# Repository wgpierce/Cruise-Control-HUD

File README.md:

# Cruise-Control-HUD
Cruise control HUD MiniProject for ECE 362 and Purdue Spark Challenge

## Setup

Configuration and project files have been omitted since they carry no useful information
and are a pain to track

If you do want to use this code yourself, using CodeWarrior, do the following:

Open CodeWarrior, and navigate through these generic dialogs.
The setting we used are right below the corresponding generic tag.

File -> New Project -> \<family\> -> \<specific member\> -> \<whichever connections\> -> Next -> Finish                  
&nbsp;&nbsp;&nbsp;&nbsp;&nbsp;&nbsp;&nbsp;&nbsp;&nbsp;&nbsp;&nbsp;&nbsp;&nbsp;&nbsp;&nbsp;&nbsp;&nbsp;&nbsp;&nbsp;&nbsp;&nbsp;&nbsp;&nbsp;&nbsp;&nbsp;&nbsp; HCS12C FAMILY &nbsp;&nbsp;&nbsp;&nbsp; MC9S12C32 &nbsp;&nbsp;&nbsp;&nbsp;&nbsp;&nbsp;&nbsp;&nbsp;&nbsp;&nbsp;&nbsp;&nbsp;&nbsp;&nbsp;&nbsp;&nbsp;&nbsp;&nbsp; USB BDM Multilink 

After that, you can just copy the code from the main.c file in this repository to replace the main.c in 
your projectFolder/Sources/ folder
		
## Technologies used

#### Hardware
- MC9S12C32 microcontroller board
- OBD to UART Cable
- LIDAR
- Custom PCB with power wired to OBD board
- Shift Registers
- 4x7-segment Displays
- Printrbot Simple Metal

#### Software
- CodeWarrior
	- USBMLT
- Eagle
- Autodesk Fusion

See Documentation for more specific details

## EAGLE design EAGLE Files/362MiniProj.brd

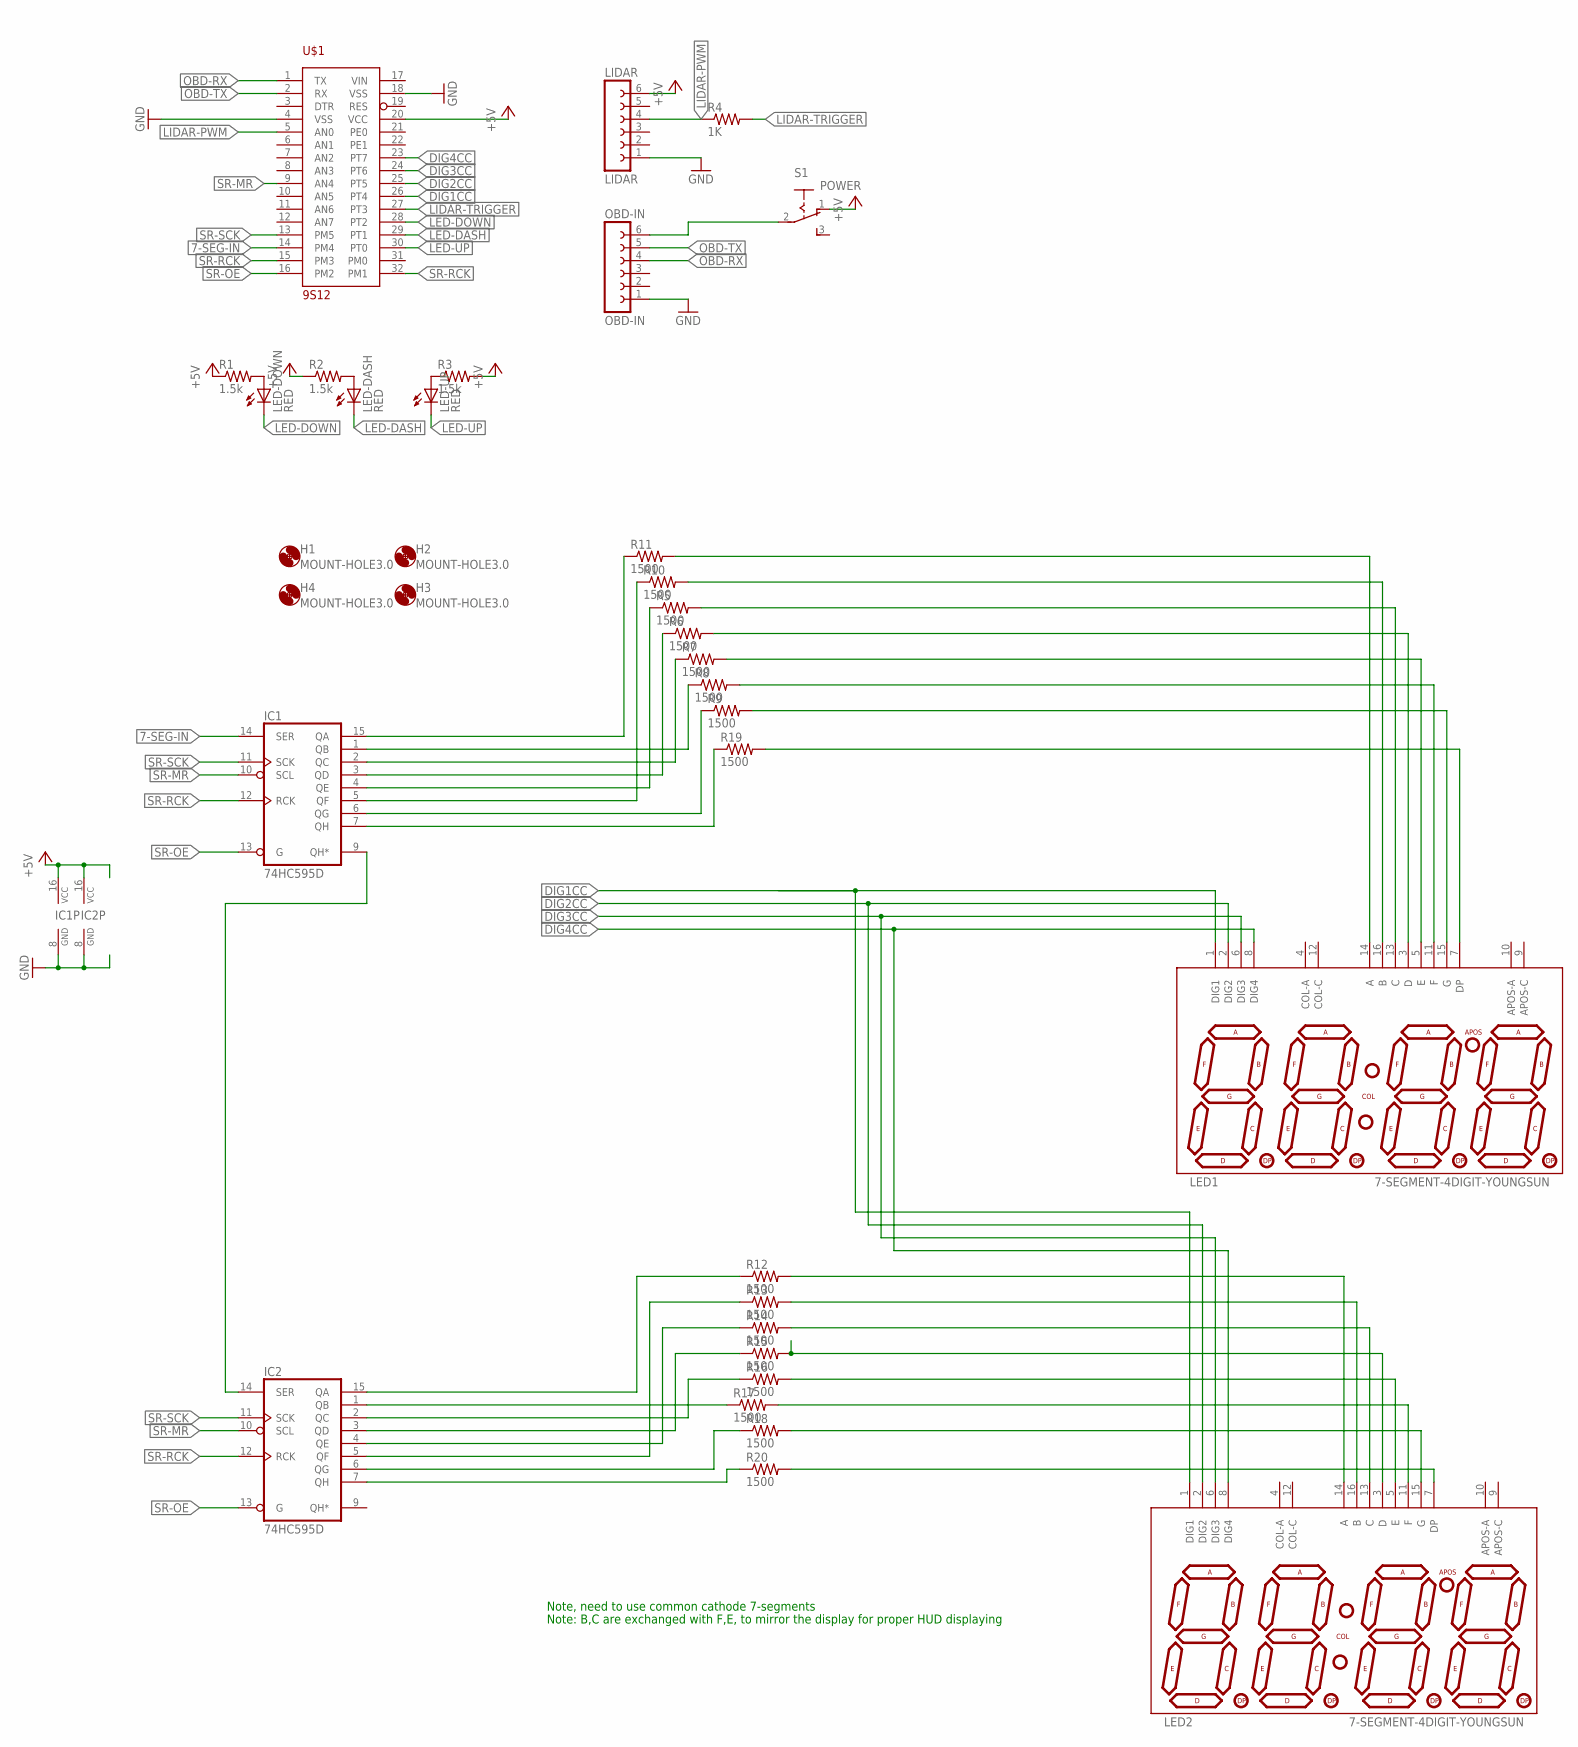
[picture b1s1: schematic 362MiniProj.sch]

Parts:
H1, H2, H3, H4: MOUNT-HOLE3.0; 3,0
IC1, IC2: 74HC595D; SO16
LED1, LED2: 7-SEGMENT-4DIGIT-YOUNGSUN
LED-DASH: RED; LED_1206
LED-DOWN: RED; LED_1206
LED-UP: RED; LED_1206
LIDAR: LIDAR; FE06
OBD-IN: OBD-IN; FE06
R1, R2, R3: 1.5k; M1206
R4: 1K; M1206
R5, R6, R7, R8, R9, R10, R11, R12, R13, R14, R15, R16, R17, R18, R19, R20: 1500; M1206
S1: POWER; M251
U$1: 9S12; DIP-32

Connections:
7-SEG-IN: IC1.14 (SER), U$1.14 (PM4)
+5V: IC1.16 (VCC), IC2.16 (VCC), LIDAR.6, R1.1, R2.1, R3.2, S1.1 (O), U$1.20 (VCC)
DIG1CC: LED1.1 (DIG1), LED2.1 (DIG1), U$1.26 (PT4)
DIG2CC: LED1.2 (DIG2), LED2.2 (DIG2), U$1.25 (PT5)
DIG3CC: LED1.6 (DIG3), LED2.6 (DIG3), U$1.24 (PT6)
DIG4CC: LED1.8 (DIG4), LED2.8 (DIG4), U$1.23 (PT7)
GND: IC1.8 (GND), IC2.8 (GND), LIDAR.1, OBD-IN.1, U$1.4 (VSS), U$1.18 (VSS)
LED-DASH: LED-DASH.C, U$1.29 (PT1)
LED-DOWN: LED-DOWN.C, U$1.28 (PT2)
LED-UP: LED-UP.C, U$1.30 (PT0)
LIDAR-PWM: LIDAR.4, R4.1, U$1.5 (AN0)
LIDAR-TRIGGER: R4.2, U$1.27 (PT3)
unnamed: IC1.9 (QH*), IC2.14 (SER)
unnamed: LED-DOWN.A, R1.2
unnamed: LED-DASH.A, R2.2
unnamed: LED-UP.A, R3.1
unnamed: IC1.15 (QA), R11.1
unnamed: IC1.1 (QB), R8.1
unnamed: IC1.2 (QC), R7.1
unnamed: IC1.4 (QE), R5.1
unnamed: IC1.3 (QD), R6.1
unnamed: IC1.5 (QF), R10.1
unnamed: IC1.6 (QG), R9.1
unnamed: IC1.7 (QH), R19.1
unnamed: IC2.7 (QH), R20.1
unnamed: LED1.14 (A), R11.2
unnamed: OBD-IN.6, S1.2
unnamed: LED2.3 (D), R15.2
unnamed: LED1.16 (B), R10.2
unnamed: LED1.13 (C), R5.2
unnamed: LED1.3 (D), R6.2
unnamed: LED1.5 (E), R7.2
unnamed: LED1.11 (F), R8.2
unnamed: LED1.15 (G), R9.2
unnamed: IC2.15 (QA), R12.1
unnamed: IC2.5 (QF), R13.1
unnamed: IC2.4 (QE), R14.1
unnamed: IC2.3 (QD), R15.1
unnamed: IC2.2 (QC), R16.1
unnamed: IC2.1 (QB), R17.1
unnamed: IC2.6 (QG), R18.1
unnamed: LED1.7 (DP), R19.2
unnamed: LED2.14 (A), R12.2
unnamed: LED2.16 (B), R13.2
unnamed: LED2.13 (C), R14.2
unnamed: LED2.5 (E), R16.2
unnamed: LED2.11 (F), R17.2
unnamed: LED2.15 (G), R18.2
unnamed: LED2.7 (DP), R20.2
OBD-RX: OBD-IN.4, U$1.1 (TX)
OBD-TX: OBD-IN.5, U$1.2 (RX)
SR-MR: IC1.10 (SCL), IC2.10 (SCL), U$1.9 (AN4)
SR-OE: IC1.13 (G), IC2.13 (G), U$1.16 (PM2)
SR-RCK: IC1.12 (RCK), IC2.12 (RCK), U$1.15 (PM3), U$1.32 (PM1)
SR-SCK: IC1.11 (SCK), IC2.11 (SCK), U$1.13 (PM5)

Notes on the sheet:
Note, need to use common cathode 7-segments
Note: B,C are exchanged with F,E, to mirror the display for proper HUD displaying

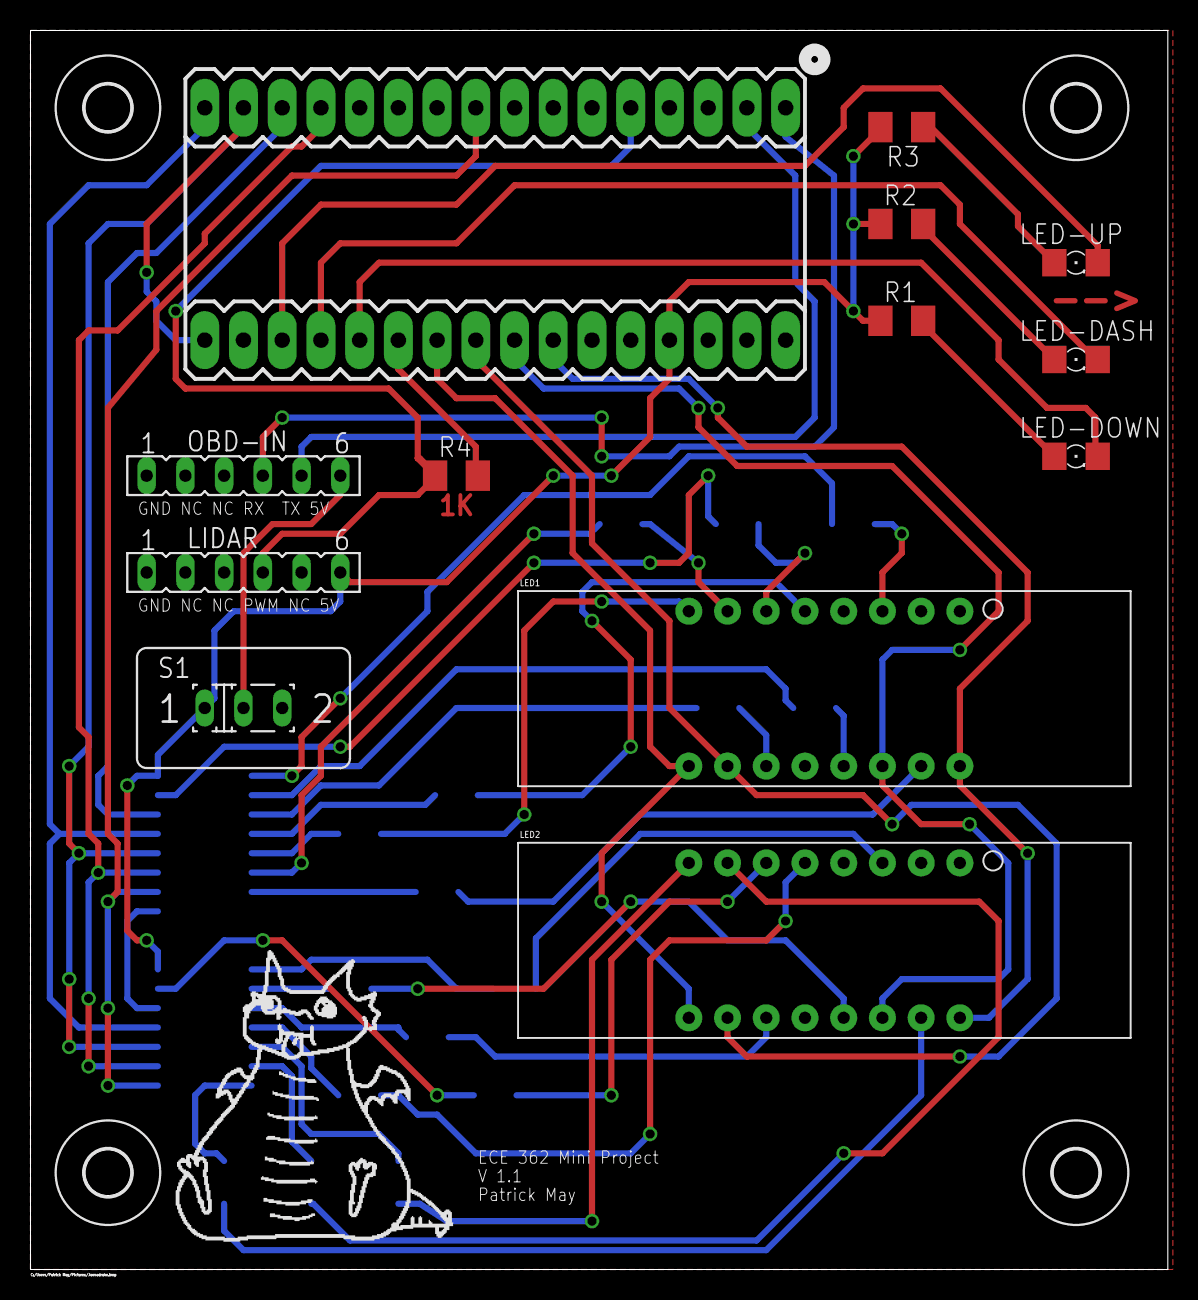
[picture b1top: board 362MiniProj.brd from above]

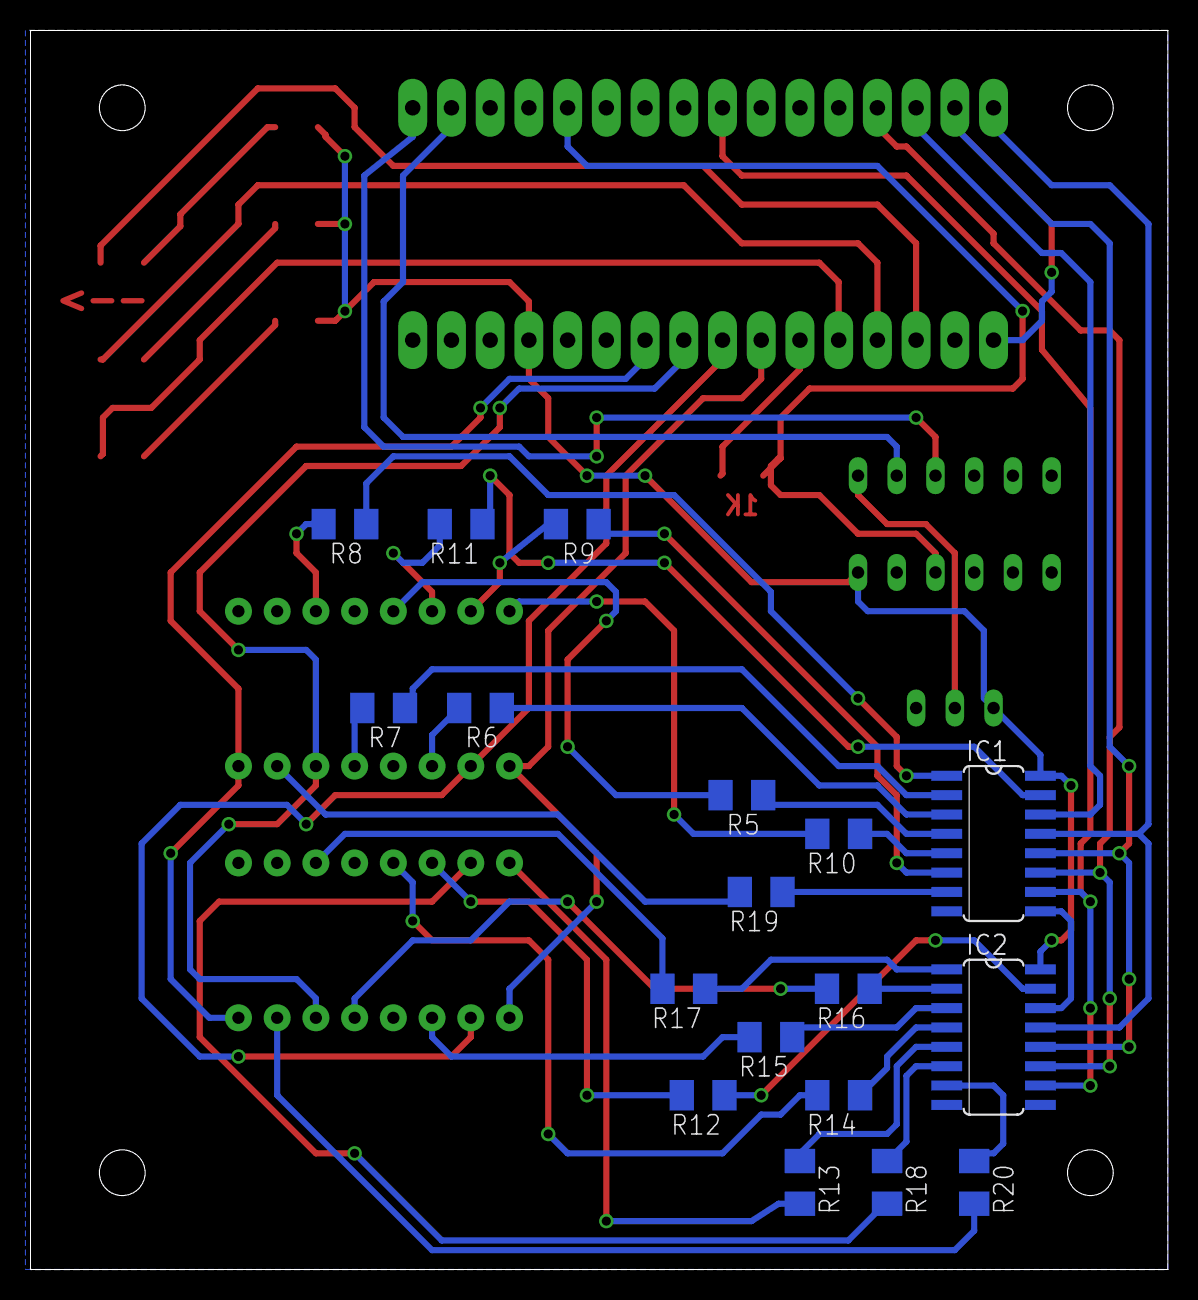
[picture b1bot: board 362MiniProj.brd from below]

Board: 2 copper layers, 74.6 x 81.3 mm, 35 parts (18 on the bottom side), 55 nets.

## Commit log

2016-11-12 Initial commit with bare CodeWarrior Project
2016-11-12 Fixed formatting, set coding standard, wrote shift register driver
2016-11-14 finished multidigit operation and adjusted timing parameters for LED driver
2016-11-18 Added serial comm functions
2016-11-21 modified LED driver so it doesn't take up processing time, wrote rudimentary LIDAR driver
2016-11-21 Added basic SCI comms, removed pushbutton sampling
2016-11-21 Added binaries
2016-11-21 Fix merge conflicts
2016-11-21 More merge conflicts
2016-11-22 Started OBD board drivers
2016-11-22 Fixed bug in search code
2016-11-30 fixed many port declarations tested LED up/down/dash disable MISO in SPI for use as GPIO pin set slave select as input to prevent shorting double-buffer LEDs (shift out 2 digits at a time) reverse di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
2016-11-30 remove object files
2016-11-30 remove bin
2016-12-01 removed all files but main.c from being tracked
2016-12-01 updated readme for creating untracked files
2016-12-01 Added finished SCI functionality
2016-12-01 Fixed compile error
2016-12-01 Added EAGLE files
2016-12-02 rewrote LIDAR driver to work now LIDAR is now based on ATD interrupts to measure for a set period of time
2016-12-02 removed dedicated LIDAR functions
2016-12-03 Tyler changed distance reading to differential speed reading
2016-12-03 changed LIDAR to only take masurement when we read measurement
2016-12-04 Fixed LIDAR bug, changed display orientation
2016-12-05 Added error checking for SCI control
2016-12-06 Fixed LIDAR drivers
2016-12-07 Added poster
2016-12-07 reorganized file organization
2016-12-07 updating poster
2016-12-07 wrote more on PPT and readme
2016-12-07 wrote more explicit documentation and fixed formatting in in main.c and updated README with relevent technologies
2016-12-07 Added contributions to poster
2016-12-08 Added km->mph conversion
2016-12-08 Updated code comments
2016-12-08 finished ppt
2016-12-08 resized and finished ppt again
2016-12-09 Added Enclosure
2016-12-09 documentation added by everyone, main.c documentation added
2016-12-09 Added contributions
2016-12-09 updated documentation word document, formatting and force casting in main.c, probably final commit
2017-05-01 fix formatting on README.md

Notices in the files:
parts and their libraries:
SparkFun-Displays: Licensing: Creative Commons ShareAlike 4.0 International - https://creativecommons.org/licenses/by-sa/4.0
